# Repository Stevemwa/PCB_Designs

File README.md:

# ALTIMETER

# IP-SNIFFER

# LCD BEEPER

# PI ZERO SENSOR SHIELD

# I2C MOTOR DRIVER

# ESP32 DEV BOARD

# ATTINY85 ALARM

# AMPLIFIER WITH TUNNING

# TELEMETRIC DASHCAM PCB

# STM32 WIFI BOARD FOR SMART BMS

# NFC MODEL TRAIN

# ROBOKEN PCB

# CAMERA TRAP PROTOTYPE

# DIMM DDR3 TESTER

# VEHICLE TRACKERS

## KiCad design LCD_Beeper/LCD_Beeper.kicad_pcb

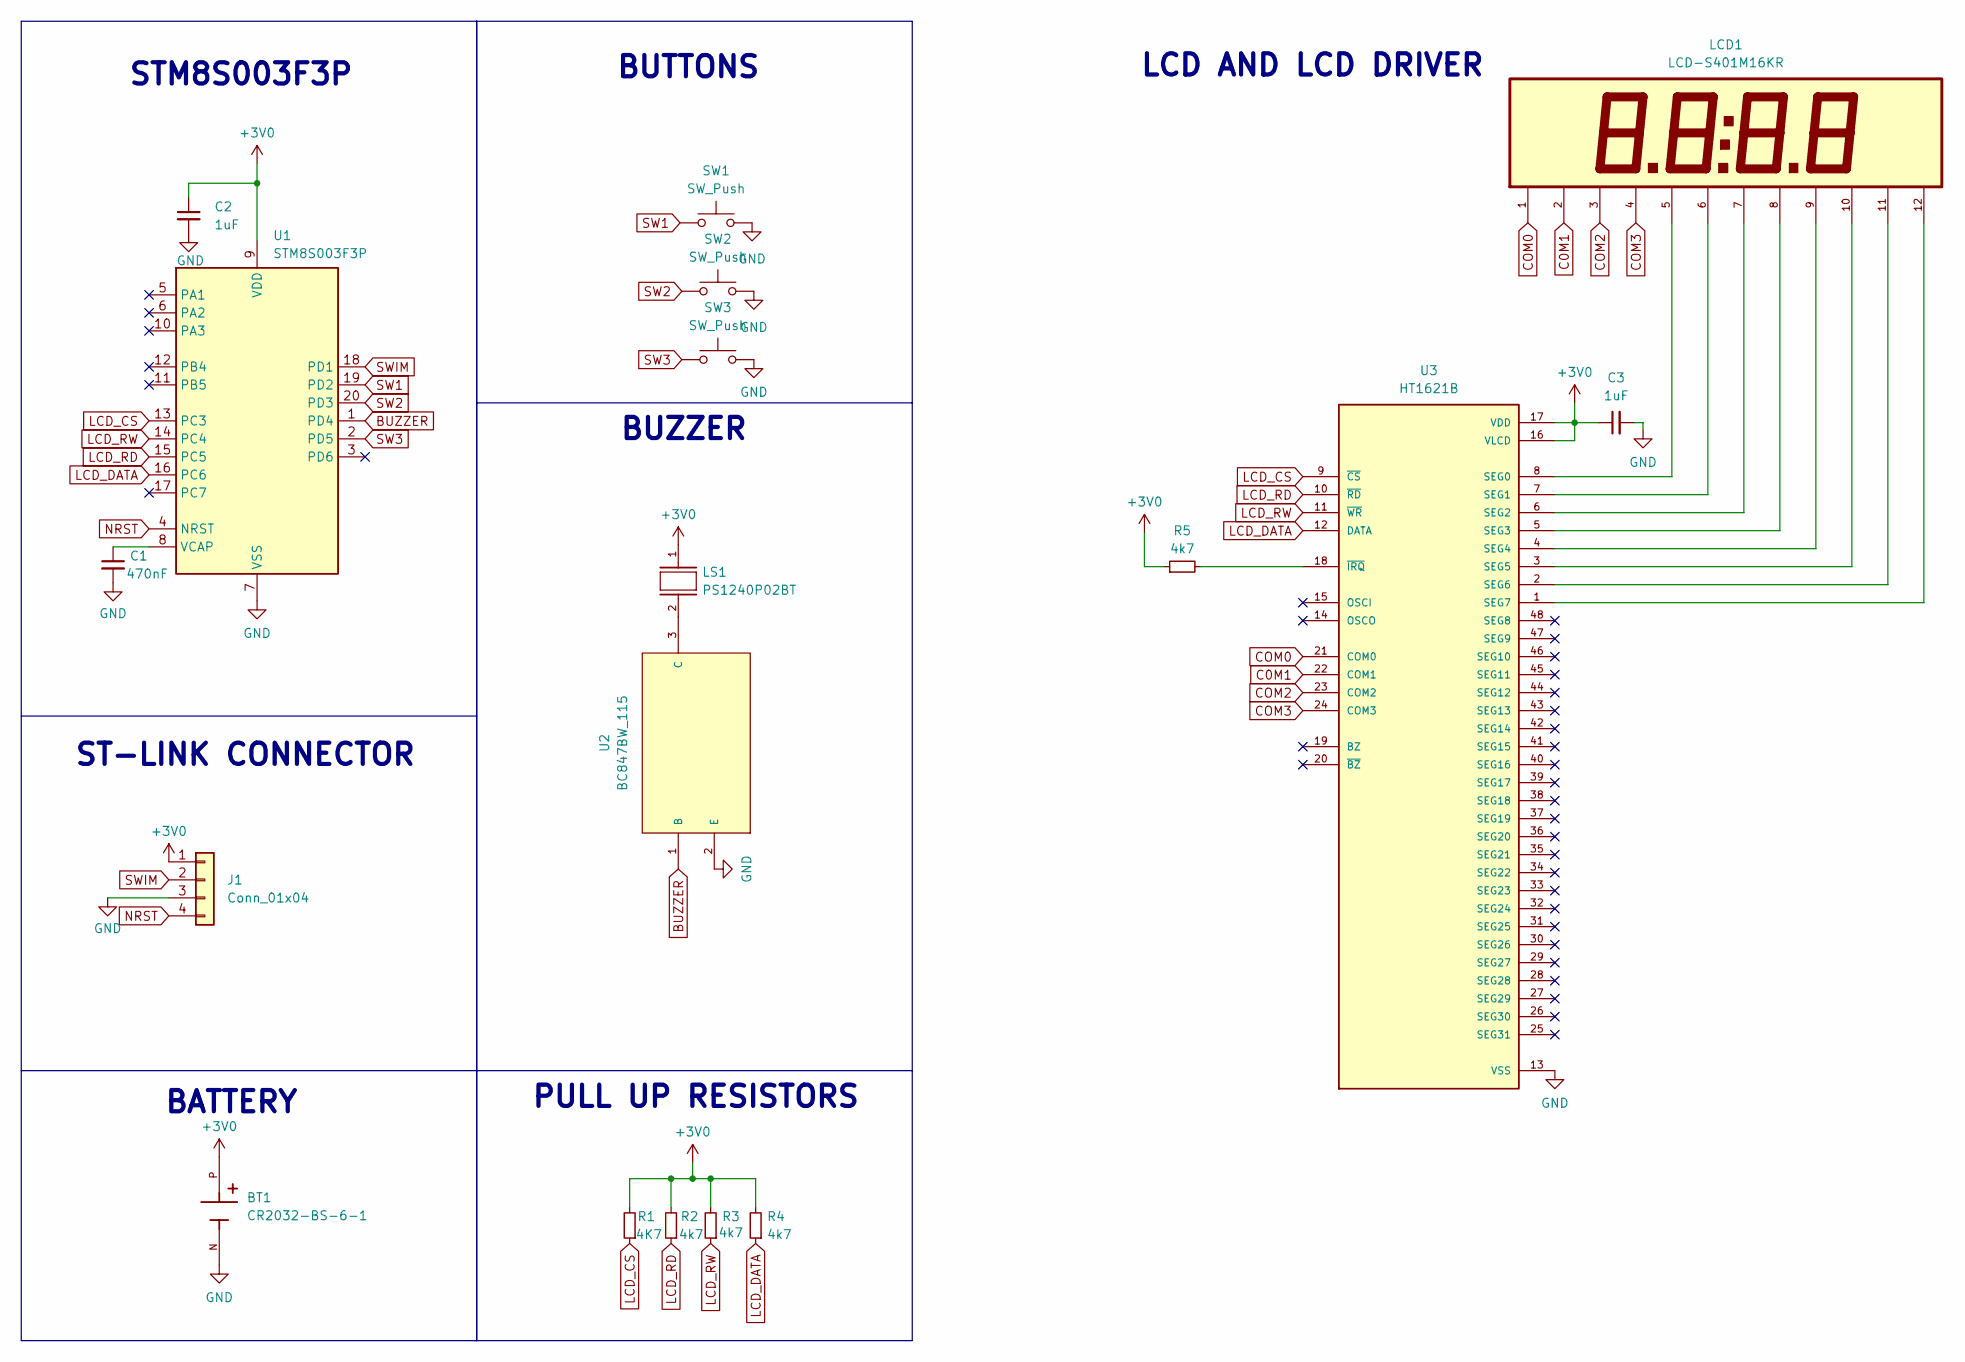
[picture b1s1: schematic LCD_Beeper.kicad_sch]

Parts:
BT1: CR2032-BS-6-1; BAT_CR2032-BS-6-1; PARTREV 2011/2/14
C1: 470nF; C_0603_1608Metric
C2, C3: 1uF; C_0805_2012Metric
J1: Conn_01x04; PinHeader_1x04_P2.54mm_Horizontal
LCD1: LCD-S401M16KR; LCD_Aliexpress
LS1: PS1240P02BT; Buzzer_PS1240P02BT
R1: 4K7; R_0603_1608Metric
R2, R3, R4, R5: 4k7; R_0603_1608Metric
SW1, SW2, SW3: SW_Push; Butn
U1: STM8S003F3P; TSSOP-20_4.4x6.5mm_P0.65mm
U2: BC847BW_115; SO65P210X100-3N; MPN BC847BW,115
U3: HT1621B; HT1621B_SOP63P1035X279-48N; PARTREV 3.21

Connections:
+3V0: BT1.P, C2.1, C3.1, J1.1, LS1.1, R1.2, R2.2, R3.2, R4.2, R5.1, U1.9 (VDD), U3.16 (VLCD), U3.17 (VDD)
BUZZER: U1.1 (PD4), U2.1 (B)
C0M1: LCD1.2, U3.22 (COM1)
COM0: LCD1.1, U3.21 (COM0)
COM2: LCD1.3, U3.23 (COM2)
COM3: LCD1.4, U3.24 (COM3)
GND: BT1.N, C1.2, C2.2, C3.2, J1.3, SW1.2, SW2.2, SW3.2, U1.7 (VSS), U2.2 (E), U3.13 (VSS)
LCD_CS: R1.1, U1.13 (PC3), U3.9 (~CS)
LCD_DATA: R4.1, U1.16 (PC6), U3.12 (DATA)
LCD_RD: R2.1, U1.15 (PC5), U3.10 (~RD)
LCD_RW: R3.1, U1.14 (PC4), U3.11 (~WR)
NRST: J1.4, U1.4 (NRST)
unnamed: C1.1, U1.8 (VCAP)
unnamed: LS1.2, U2.3 (C)
unnamed: LCD1.5, U3.8 (SEG0)
unnamed: LCD1.6, U3.7 (SEG1)
unnamed: LCD1.7, U3.6 (SEG2)
unnamed: LCD1.8, U3.5 (SEG3)
unnamed: LCD1.9, U3.4 (SEG4)
unnamed: LCD1.10, U3.3 (SEG5)
unnamed: LCD1.11, U3.2 (SEG6)
unnamed: LCD1.12, U3.1 (SEG7)
unnamed: R5.2, U3.18 (~IRQ)
SW1: SW1.1, U1.19 (PD2)
SW2: SW2.1, U1.20 (PD3)
SW3: SW3.1, U1.2 (PD5)
SWIM: J1.2, U1.18 (PD1)

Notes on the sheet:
PULL UP RESISTORS
LCD AND LCD DRIVER
BUTTONS
ST-LINK CONNECTOR
STM8S003F3P
BATTERY
BUZZER

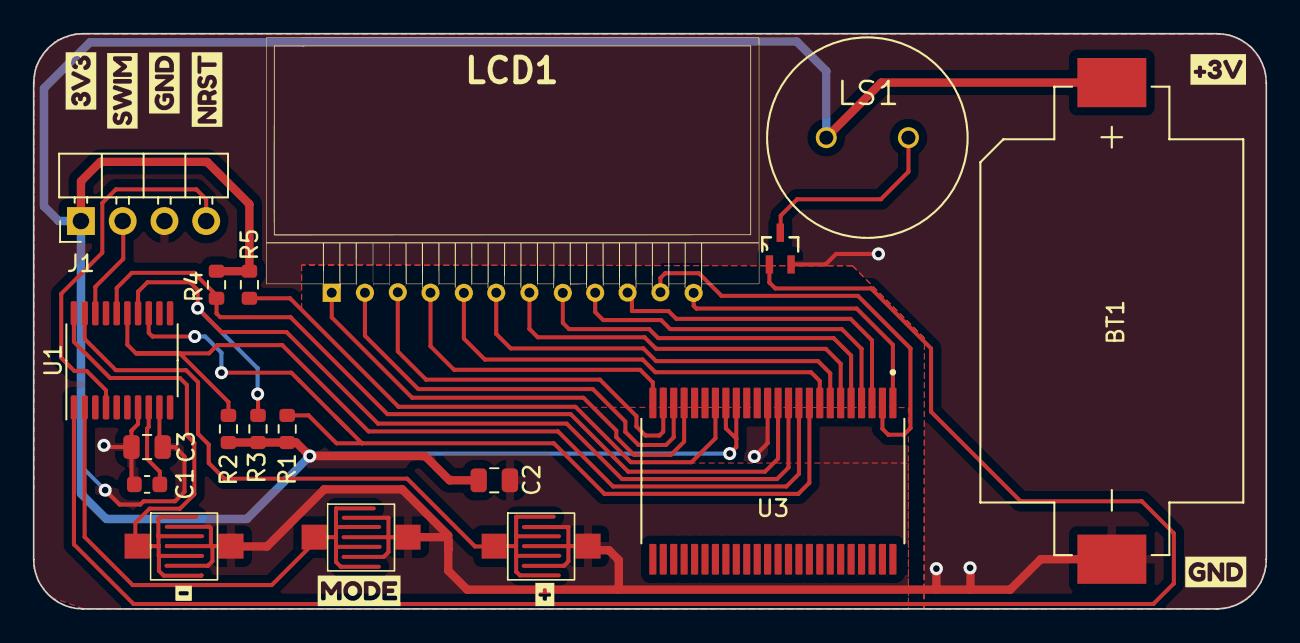
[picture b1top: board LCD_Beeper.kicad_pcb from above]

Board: 2 copper layers, 75.0 x 35.0 mm, 27 parts (0 on the bottom side), 27 nets.

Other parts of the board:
kibuzzard-669CD0A9: G***; kibuzzard-669CD0A9
kibuzzard-669CD0BB: G***; kibuzzard-669CD0BB
kibuzzard-669CD0D2: G***; kibuzzard-669CD0D2
kibuzzard-669CD0EA: G***; kibuzzard-669CD0EA
kibuzzard-669D55EF: G***; kibuzzard-669D55EF
kibuzzard-669D561E: G***; kibuzzard-669D561E
kibuzzard-669D5618: G***; kibuzzard-669D5618
kibuzzard-669E5857: G***; kibuzzard-669E5857
kibuzzard-669E5870: G***; kibuzzard-669E5870

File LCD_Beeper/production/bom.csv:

Designator,Footprint,Quantity,Value,JLCPCB Part #
BT1,SMD,1,CR2032-BS-6-1,C70377
C1,603,1,50V 470nF X7R ±10%,C77572
"C2, C3",805,2,1uF,C89259
J1,"Push-Pull,P=2.54mm",1,PinHeader_1x04_P2.54mm_Horizontal,C91552
LS1,"Plugin,D=12.2mm",1,PS1240P02BT,C76871
"R1, R2, R3, R4, R5",603,5,50V ±25ppm/? ±0.1% 4.7k? 0603 ,C666997
"SW1, SW2, SW3",Butn,3,SW_Push,
U1,TSSOP-20,1,STM8S003F3P,C18615
U2,SOT-323,1,BC847BW_115,C2836072
U3,SSOP-48-300mil,1,HT1621B,C7873

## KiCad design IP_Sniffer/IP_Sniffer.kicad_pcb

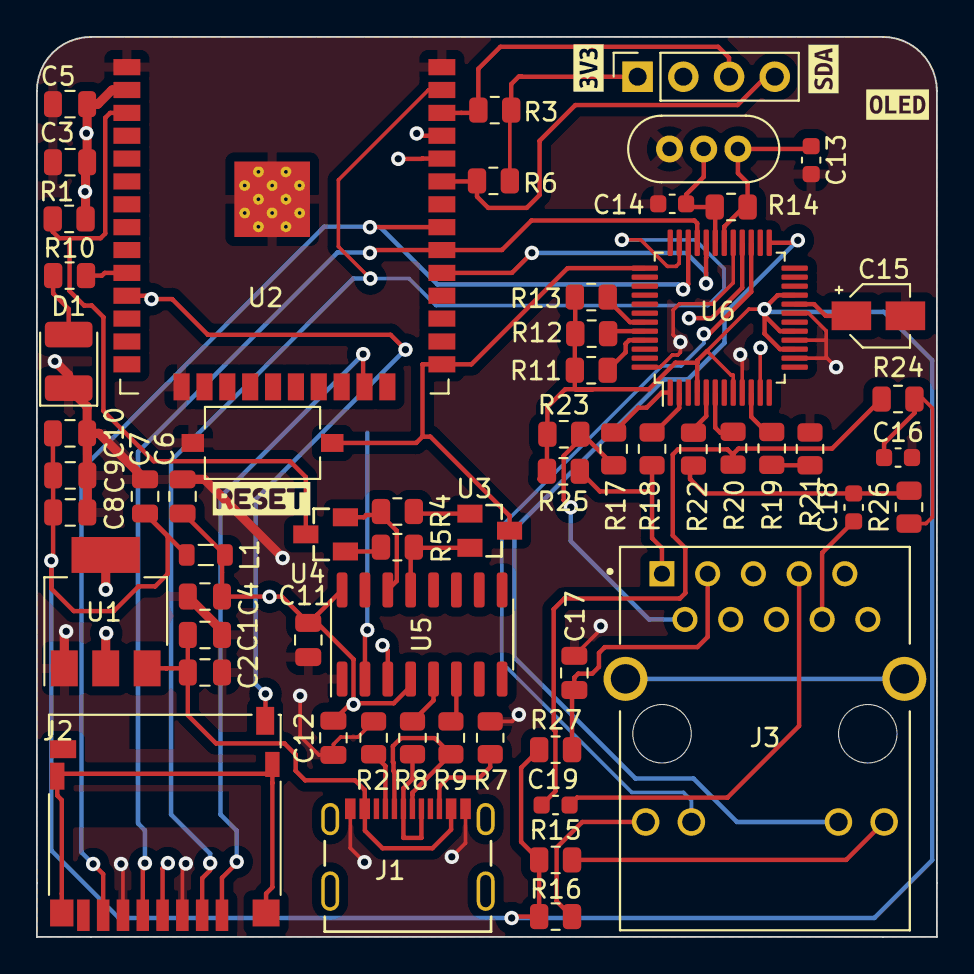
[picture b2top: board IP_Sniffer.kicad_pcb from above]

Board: 4 copper layers, 50.0 x 50.0 mm, 64 parts (0 on the bottom side), 52 nets.

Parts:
C1, C6: 100uF; C_0805_2012Metric
C2, C4, C7, C8, C9, C12: 100nF; C_0805_2012Metric
C3: 1uF; C_0805_2012Metric
C5, C10: 10uF; C_0805_2012Metric
C11: 100nf; C_0805_2012Metric
C13, C14: 12pF; C_0603_1608Metric
C15: 4u7; CP_Elec_3x5.3
C16: 10n; C_0603_1608Metric
C17: 100n; C_0805_2012Metric
C18, C19: 6.8n; C_0603_1608Metric
D1: LED_Small; LED_1210_3225Metric_Pad1.42x2.65mm_HandSolder
J1: 2171790001; USB_C_MOLEX
J2: SD_Card; microSD_HC_Hirose_DM3D-SF
J3: HR911130A; RJ45_HANRUN_HR911130A
J4: Conn_01x04; PinSocket_1x04_P2.54mm_Vertical
L1: 10uH; L_0805_2012Metric
R1, R2, R3, R6, R7, R10, R19, R21: 5k1; R_0805_2012Metric
R4, R5, R11, R12, R13: 10k; R_0805_2012Metric
R8, R9, R17, R18, R20, R22: 33; R_0805_2012Metric
R14: 1M; R_0805_2012Metric
R15, R16: 330R; R_0805_2012Metric
R23, R24, R25, R26: 49R9/1%; R_0805_2012Metric
R27: 10R/1%; R_0805_2012Metric
SW1: SW_Push; SW_Tactile_SPST_NO_Straight_CK_PTS636Sx25SMTRLFS
U1: AMS1117; SOT-223-3_TabPin2
U2: ESP32-WROOM-32
U3, U4: IRLML2502TRPBF; SOT23
U5: CH340C; SOIC-16_3.9x9.9mm_P1.27mm
U6: W5500; LQFP-48_7x7mm_P0.5mm
Y1: 25MHz; Crystal_HC52-U-3Pin_Vertical
kibuzzard-66784B35: G***; kibuzzard-66784B35
kibuzzard-667847D2: G***; kibuzzard-667847D2
kibuzzard-667847FB: G***; kibuzzard-667847FB
kibuzzard-667858E3: G***; kibuzzard-667858E3

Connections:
+3.3VA: C7.1, C8.1, C9.1, C10.1, L1.2, R11.1, R12.1, R13.1, R15.1, R16.1, R23.2, R25.2, R27.2, U6.4 (AVDD), U6.8 (AVDD), U6.11 (AVDD), U6.15 (AVDD), U6.17 (AVDD), U6.21 (AVDD)
+3V3: C3.1, C4.1, C5.1, C6.1, C11.2, C12.1, J2.4 (VDD), J4.1, L1.1, R1.1, R3.1, R6.1, U1.2 (VO), U2.2 (VDD), U5.4 (V3), U5.16 (VCC), U6.28 (VDD)
+5V: C1.1, C2.1, J1.A4B9 (VBUS1), J1.B4A9 (VBUS2), U1.3 (VI)
CARD_DETECT: J2.10 (CARD_DETECT), U2.11 (IO26)
DTR: R5.1, U3.2, U5.13 (~DTR)
EN: R1.2, U2.3 (EN), U4.3
ESP-RX: U2.34 (RXD0/IO3), U5.2 (TXD)
ESP-TX: U2.35 (TXD0/IO1), U5.3 (RXD)
GND: C1.2, C2.2, C3.2, C4.2, C5.2, C6.2, C7.2, C8.2, C9.2, C10.2, C11.1, C12.2, C13.2, C14.1, C15.2, C16.2, C17.2, D1.1 (K), J1.A1B12 (GND1), J1.B1A12 (GND2), J2.3 (VSS), J2.6 (VSS), J4.2, R2.1, R7.2, R21.2, SW1.2, U1.1 (ADJ), U2.1 (GND), U2.15 (GND), U2.38 (GND), U2.39 (GND), U5.1 (GND), U6.3 (AGND), U6.9 (AGND), U6.14 (AGND), U6.16 (AGND), U6.19 (AGND), U6.29 (GND), U6.48 (AGND), Y1.3
IO0: SW1.1, U2.25 (IO0), U3.3, U6.37 (~RST)
IO25: R10.1, U2.10 (IO25)
MISO: J2.7 (DAT0), U2.31 (IO19), U6.34 (MISO)
MOSI: J2.2 (CMD), U2.37 (IO23), U6.35 (MOSI)
unnamed: C16.1, R24.1, R26.1
unnamed: C18.1, R22.1, R26.2
unnamed: C19.1, R20.2, R24.2
unnamed: D1.2 (A), R10.2
unnamed: J1.A5 (CC1), R2.2
unnamed: J1.B5 (CC2), R7.1
unnamed: J3.11, R16.2
unnamed: J3.14, R15.2
unnamed: R4.2, U3.1
unnamed: R5.2, U4.1
unnamed: R19.2, R21.1
unnamed: R8.2, U5.5 (UD+)
unnamed: R9.2, U5.6 (UD-)
unnamed: R19.1, U6.10 (EXRES1)
unnamed: R11.2, U6.45 (PMODE0)
unnamed: R12.2, U6.44 (PMODE1)
unnamed: R13.2, U6.43 (PMODE2)
unnamed: R22.2, U6.5 (RXN)
unnamed: R20.1, U6.6 (RXP)
unnamed: C15.1, U6.20 (TOCAP)
unnamed: R17.2, U6.1 (TXN)
unnamed: R18.1, U6.2 (TXP)
unnamed: C13.1, R14.2, U6.30 (XI/CLKIN), Y1.1
unnamed: C14.2, R14.1, U6.31 (XO), Y1.2
R1: J3.1, R18.2, R25.1
R2: J3.2, R17.1, R23.1
R3: C17.1, J3.3, R27.1
R7: C19.2, J3.7
R8: C18.2, J3.8
RTS: R4.1, U4.2, U5.14 (~RTS)
SCK: J2.5 (CLK), U2.30 (IO18), U6.33 (SCLK)
SCL: J4.3, R3.2, U2.36 (IO22)
SDA: J4.4, R6.2, U2.33 (IO21)
SS1: U2.29 (IO5), U6.32 (~SCS)
SS2: J2.1 (CD/DAT3), U2.23 (IO15)
USB_D+: J1.A6 (DP1), J1.B6 (DP2), R8.1
USB_D-: J1.A7 (DN1), J1.B7 (DN2), R9.1
actled: J3.12, U6.27 (ACTLED)
linkled: J3.13, U6.25 (LINKLED)

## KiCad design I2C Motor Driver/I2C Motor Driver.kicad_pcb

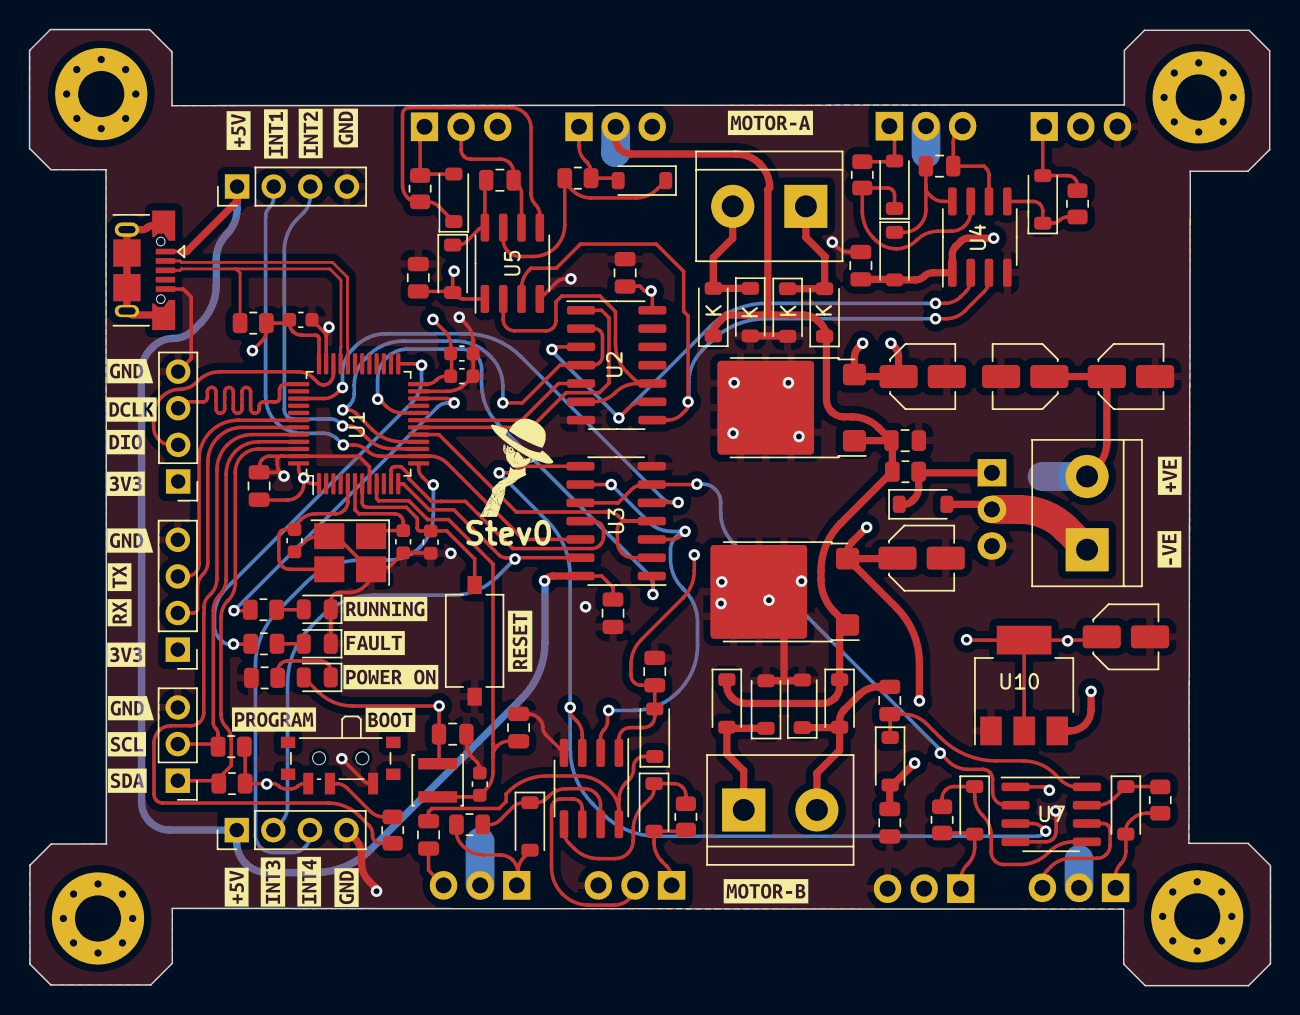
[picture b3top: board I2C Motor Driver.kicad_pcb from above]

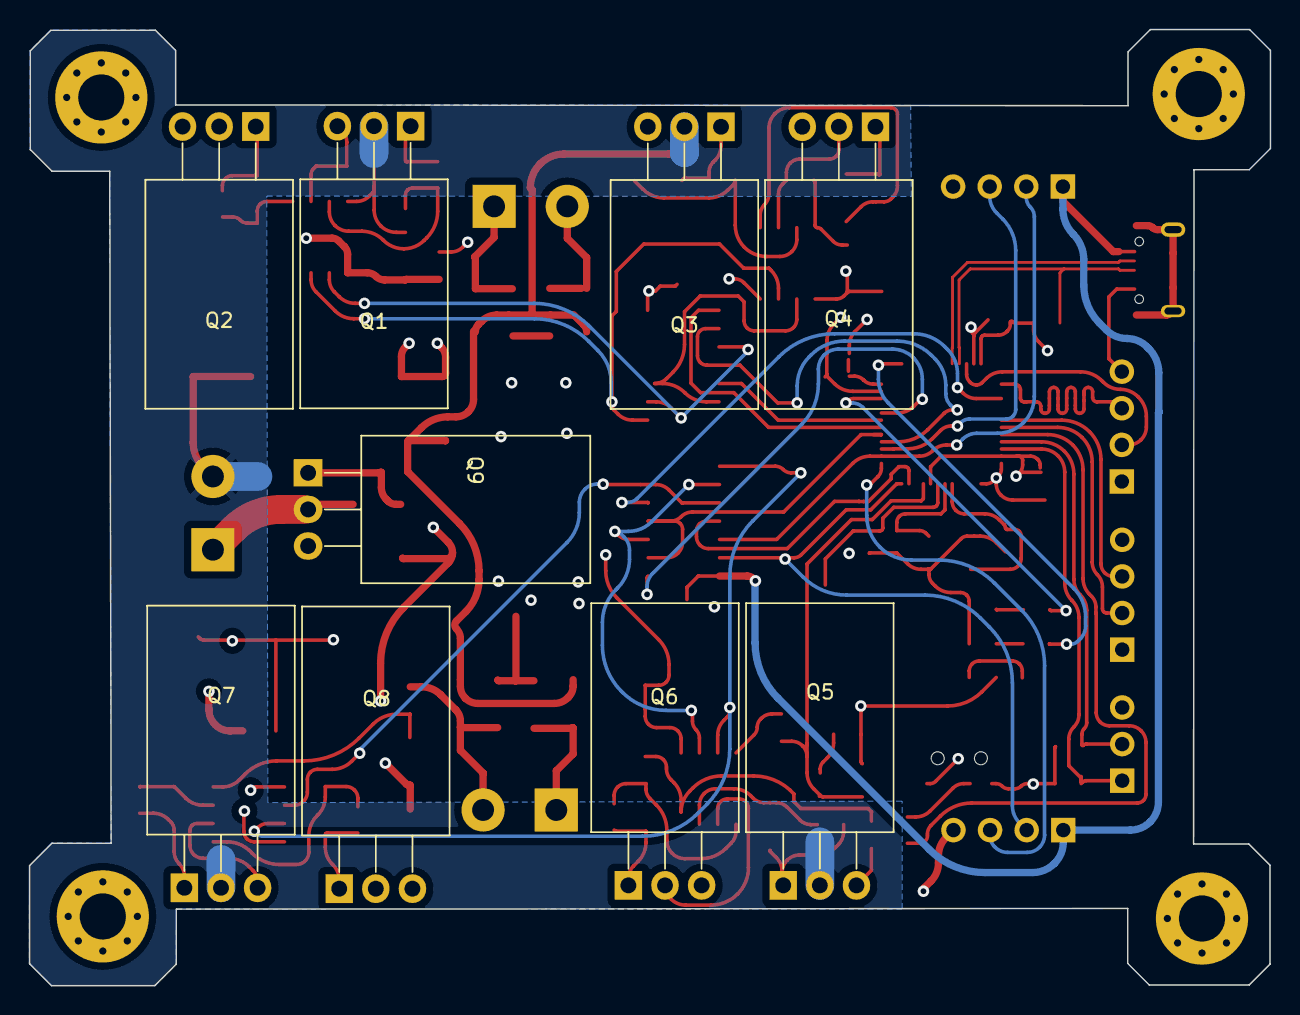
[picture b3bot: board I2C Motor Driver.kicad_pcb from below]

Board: 4 copper layers, 86.1 x 66.3 mm, 132 parts (9 on the bottom side), 67 nets.

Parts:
C1, C22: 10uF; C_0805_2012Metric
C2, C3, C4, C8: 100nF; C_0603_1608Metric
C5, C7, C11, C14, C15, C18, C25, C26: 1uF; C_0805_2012Metric
C6: 10nF; C_0603_1608Metric
C9, C10: 10pF; C_0603_1608Metric
C12, C13, C16, C17: 1.5uF; C_0805_2012Metric
C19: 100uF; C_Elec_4x5.4
C20, C21, C23, C24: 22uF; C_Elec_4x5.4
D1: BLUE; LED_0805_2012Metric
D2: GREEN; LED_0805_2012Metric
D3, D12, D13, D22: D; D_SOD-123
D4, D5, D10, D11, D14, D15, D20, D21: 1N4148; D_SOD-123
D6, D7, D8, D9, D16, D17, D18, D19: 1N5819; D_SOD-123
D23: 15v; D_SOD-123
D24: RED; LED_0805_2012Metric
FB1: 120R; L_Changjiang_FNR3010S
H1, H2, H3, H4: MountingHole_Pad; MountingHole_3.2mm_M3_Pad_Via
J1, J3: SWD; PinHeader_1x04_P2.54mm_Vertical
J2, J6: Conn_01x04_Pin; PinHeader_1x04_P2.54mm_Vertical
J4: Conn_01x03_Pin; PinHeader_1x03_P2.54mm_Vertical
J5: USB_B_Micro; USB_Micro-B_XKB_U254-051T-4BH83-F1S
J7: MOTOR_A; TerminalBlock_bornier-2_P5.08mm
J8: MOTOR_B; TerminalBlock_bornier-2_P5.08mm
J9: +24V_INPUT; TerminalBlock_bornier-2_P5.08mm
Q1, Q2, Q3, Q4, Q5, Q6, Q7, Q8, Q9: IRLZ44N; TO-220-3_Horizontal_TabDown
R1, R15: 10k; R_0805_2012Metric
R2, R3, R4, R5, R6, R16: 1K5; R_0805_2012Metric
R7, R8, R9, R10, R11, R12, R13, R14: 30R; R_0805_2012Metric
SW1: SW_DPST_x2; SW_Tactile_SPST_NO_Straight_CK_PTS636Sx25SMTRLFS
SW2: SW_SPDT; SW_SPDT_PCM12
Stev0: LOGO; Luffy6by6
U1: STM32F103C8Tx; LQFP-48_7x7mm_P0.5mm
U2, U3: 7400; SOIC-14_3.9x8.7mm_P1.27mm
U4, U5, U6, U7: IR2104; SOIC-8_3.9x4.9mm_P1.27mm
U8: L7805; ATPAK-2
U9: L7815; ATPAK-2
U10: AMS1117-3.3; SOT-223-3_TabPin2
Y1: 16MHz; Crystal_SMD_3225-4Pin_3.2x2.5mm_HandSoldering
kibuzzard-664F1B6E: G***; kibuzzard-664F1B6E
kibuzzard-664F1B57: G***; kibuzzard-664F1B57
kibuzzard-664F4C94: G***; kibuzzard-664F4C94
kibuzzard-664F4D60: G***; kibuzzard-664F4D60
kibuzzard-664F4D77: G***; kibuzzard-664F4D77
kibuzzard-664F4DB5: G***; kibuzzard-664F4DB5
kibuzzard-664F4E3A: G***; kibuzzard-664F4E3A
kibuzzard-664F4F6B: G***; kibuzzard-664F4F6B
kibuzzard-664F4F90: G***; kibuzzard-664F4F90
kibuzzard-664F19CD: G***; kibuzzard-664F19CD
kibuzzard-664F19D9: G***; kibuzzard-664F19D9
kibuzzard-664F19F6, kibuzzard-664F19F6#2: G***; kibuzzard-664F19F6
kibuzzard-664F35B9: G***; kibuzzard-664F35B9
kibuzzard-664F47C9: G***; kibuzzard-664F47C9
kibuzzard-664F49B2: G***; kibuzzard-664F49B2
kibuzzard-664F49D0: G***; kibuzzard-664F49D0
kibuzzard-664F52A3: G***; kibuzzard-664F52A3
kibuzzard-664F52AD: G***; kibuzzard-664F52AD
kibuzzard-664F88B5: G***; kibuzzard-664F88B5
kibuzzard-664F88D1: G***; kibuzzard-664F88D1
kibuzzard-664F88FA: G***; kibuzzard-664F88FA
kibuzzard-664F354C: G***; kibuzzard-664F354C
kibuzzard-664F878C: G***; kibuzzard-664F878C
kibuzzard-664F3565: G***; kibuzzard-664F3565
kibuzzard-664F8782: G***; kibuzzard-664F8782
kibuzzard-664F8796: G***; kibuzzard-664F8796
kibuzzard-664F8901: G***; kibuzzard-664F8901
kibuzzard-664FF9FF: G***; kibuzzard-664FF9FF

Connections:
+3.3V: C1.1, C2.1, C3.1, C4.1, C7.1, C24.1, D24.2 (A), FB1.1, J1.1, J3.1, R2.2, R5.2, R6.2, SW2.3 (C), U1.1 (VBAT), U1.24 (VDD), U1.36 (VDD), U1.48 (VDD), U10.2 (VO)
+5V: C21.1, C25.1, C26.1, J2.1, J5.1 (VBUS), J6.1, U2.14 (VCC), U3.14 (VCC), U8.3 (OUT)
+15V: C11.1, C14.1, C15.1, C18.1, C23.1, D3.2 (A), D12.2 (A), D13.2 (A), D22.2 (A), U4.1 (VCC), U5.1 (VCC), U6.1 (VCC), U7.1 (VCC), U9.3 (OUT), U10.3 (VI)
+24V: C19.1, C20.1, C22.1, D6.1 (K), D8.1 (K), D16.1 (K), D18.1 (K), J9.2, Q1.2 (D), Q3.2 (D), Q5.2 (D), Q7.2 (D), R15.1, U8.1 (IN), U9.1 (IN)
/Dual_HBridge/HC1: C16.2, D16.2 (A), D17.1 (K), J8.1, Q5.3 (S), Q6.2 (D), U6.6 (VS)
/Dual_HBridge/HC2: C17.2, D18.2 (A), D19.1 (K), J8.2, Q7.3 (S), Q8.2 (D), U7.6 (VS)
/Dual_HBridge/HC3: C12.2, D6.2 (A), D7.1 (K), J7.1, Q1.3 (S), Q2.2 (D), U4.6 (VS)
/Dual_HBridge/HC4: C13.2, D8.2 (A), D9.1 (K), J7.2, Q3.3 (S), Q4.2 (D), U5.6 (VS)
BLUE_LED: R3.1, U1.25 (PB12)
BOOT0: R1.2, U1.44 (BOOT0)
ENA: U1.16 (PA6), U2.2, U2.4
ENB: U1.17 (PA7), U3.2, U3.4
EXT_INT0: U1.11 (PA1), U3.11
EXT_INT1: J2.2, U1.14 (PA4), U3.12
EXT_INT2: J2.3, U1.15 (PA5)
EXT_INT3: J6.2, U1.12 (PA2), U3.13
EXT_INT4: J6.3, U1.13 (PA3)
GND: C1.2, C2.2, C3.2, C4.2, C5.2, C6.2, C7.2, C8.2, C9.2, C10.2, C11.2, C14.2, C15.2, C18.2, C19.2, C20.2, C21.2, C22.2, C23.2, C24.2, C25.2, C26.2, D1.1 (K), D2.1 (K), D7.2 (A), D9.2 (A), D17.2 (A), D19.2 (A), J1.4, J2.4, J3.4, J4.3, J5.5 (GND), J6.4, Q2.3 (S), Q4.3 (S), Q6.3 (S), Q8.3 (S), Q9.3 (S), R16.2, SW1.1 (A), SW2.1 (A), U1.8 (VSSA), U1.23 (VSS), U1.35 (VSS), U1.47 (VSS), U2.7 (GND), U3.7 (GND), U4.4 (COM), U5.4 (COM), U6.4 (COM), U7.4 (COM), U8.2 (GND), U9.2 (GND), U10.1 (GND), Y1.2, Y1.4
GREEN_LED: R4.1, U1.22 (PB11)
HSE_IN: C10.1, U1.5 (PD0), Y1.3
HSE_OUT: C9.1, U1.6 (PD1), Y1.1
I2C_SCL: J4.2, R5.1, U1.45 (PB8)
I2C_SDA: J4.1, R6.1, U1.46 (PB9)
IN1: U1.18 (PB0), U2.1
IN2: U1.19 (PB1), U2.5
IN3: U1.20 (PB2), U3.1
IN4: U1.39 (PB3), U3.5
NRST: C8.1, SW1.2 (B), U1.7 (NRST)
unnamed: D1.2 (A), R3.2
unnamed: D2.2 (A), R4.2
unnamed: C12.1, D3.1 (K), U4.8 (VB)
unnamed: D4.2 (A), Q2.1 (G), R7.2
unnamed: D4.1 (K), R7.1, U4.5 (LO)
unnamed: D5.2 (A), Q1.1 (G), R8.2
unnamed: D5.1 (K), R8.1, U4.7 (HO)
unnamed: D10.2 (A), Q3.1 (G), R9.2
unnamed: D10.1 (K), R9.1, U5.7 (HO)
unnamed: D11.2 (A), Q4.1 (G), R10.2
unnamed: D11.1 (K), R10.1, U5.5 (LO)
unnamed: C13.1, D12.1 (K), U5.8 (VB)
unnamed: C16.1, D13.1 (K), U6.8 (VB)
unnamed: D14.2 (A), Q6.1 (G), R11.2
unnamed: D14.1 (K), R11.1, U6.5 (LO)
unnamed: D15.2 (A), Q5.1 (G), R12.2
unnamed: D15.1 (K), R12.1, U6.7 (HO)
unnamed: D20.2 (A), Q7.1 (G), R13.2
unnamed: D20.1 (K), R13.1, U7.7 (HO)
unnamed: D21.2 (A), Q8.1 (G), R14.2
unnamed: D21.1 (K), R14.1, U7.5 (LO)
unnamed: C17.1, D22.1 (K), U7.8 (VB)
unnamed: D23.2 (A), J9.1, Q9.2 (D)
unnamed: D23.1 (K), Q9.1 (G), R15.2
unnamed: D24.1 (K), R16.1
unnamed: R1.1, SW2.2 (B)
unnamed: C5.1, C6.1, FB1.2, U1.9 (VDDA)
unnamed: U2.3, U2.9, U4.2 (IN)
unnamed: U2.8, U4.3 (~SD), U5.3 (~SD)
unnamed: U2.6, U2.10, U5.2 (IN)
unnamed: U3.3, U3.9, U6.2 (IN)
unnamed: U3.8, U6.3 (~SD), U7.3 (~SD)
unnamed: U3.6, U3.10, U7.2 (IN)
SWCLK: J1.3, U1.37 (PA14)
SWDIO: J1.2, U1.34 (PA13)
UART1_RX: J3.2, U1.43 (PB7)
UART1_TX: J3.3, U1.42 (PB6)
USB_D+: J5.3 (D+), R2.1, U1.33 (PA12)
USB_D-: J5.2 (D-), U1.32 (PA11)

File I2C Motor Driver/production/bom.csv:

Designator,Footprint,Quantity,Value,LCSC Part #
"C1, C22",0805,2,10uF,
"C10, C9",0603,2,10pF,
"C11, C14, C15, C18, C5, C7",0805,6,1uF,
"C12, C13, C16, C17",0805,4,1.5uF,
C19,C_Elec_4x5.4,1,100uF,
"C2, C3, C4, C8",0603,4,100nF,
"C20, C21, C23, C24",C_Elec_4x5.4,4,22uF,
C6,0603,1,10nF,
D1,0805,1,BLUE,
"D10, D11, D14, D15, D20, D21, D4, D5",D_SOD-123,8,1N4148,
"D12, D13, D22, D3",D_SOD-123,4,D,
"D16, D17, D18, D19, D6, D7, D8, D9",D_SOD-123,8,1N5819,
D2,0805,1,GREEN,
D23,D_SOD-123,1,15v,
D24,0805,1,RED,
FB1,L_Changjiang_FNR3010S,1,120R,
"H1, H2, H3, H4",MountingHole_3.2mm_M3_Pad_Via,4,MountingHole_Pad,
"J1, J3",PinHeader_1x04_P2.54mm_Vertical,2,SWD,
"J2, J6",PinHeader_1x04_P2.54mm_Vertical,2,Conn_01x04_Pin,
J4,PinHeader_1x03_P2.54mm_Vertical,1,Conn_01x03_Pin,
J5,USB_Micro-B_XKB_U254-051T-4BH83-F1S,1,USB_B_Micro,
J7,TerminalBlock_bornier-2_P5.08mm,1,MOTOR_A,
J8,TerminalBlock_bornier-2_P5.08mm,1,MOTOR_B,
J9,TerminalBlock_bornier-2_P5.08mm,1,+24V_INPUT,
"Q1, Q2, Q3, Q4, Q5, Q6, Q7, Q8, Q9",TO-220-3_Horizontal_TabDown,9,IRLZ44N,
"R1, R15",0805,2,10k,
"R10, R11, R12, R13, R14, R7, R8, R9",0805,8,30R,
"R16, R2, R3, R4, R5, R6",0805,6,1K5,
SW1,SW_Tactile_SPST_NO_Straight_CK_PTS636Sx25SMTRLFS,1,SW_DPST_x2,
SW2,SW_SPDT_PCM12,1,SW_SPDT,
U1,LQFP-48_7x7mm_P0.5mm,1,STM32F103C8Tx,
U10,SOT-223-3_TabPin2,1,AMS1117-3.3,
"U2, U3",SOIC-14_3.9x8.7mm_P1.27mm,2,7400,
"U4, U5, U6, U7",SOIC-8_3.9x4.9mm_P1.27mm,4,IR2104,
U8,ATPAK-2,1,L7805,
U9,ATPAK-2,1,L7815,
Y1,Crystal_SMD_3225-4Pin_3.2x2.5mm_HandSoldering,1,16MHz,

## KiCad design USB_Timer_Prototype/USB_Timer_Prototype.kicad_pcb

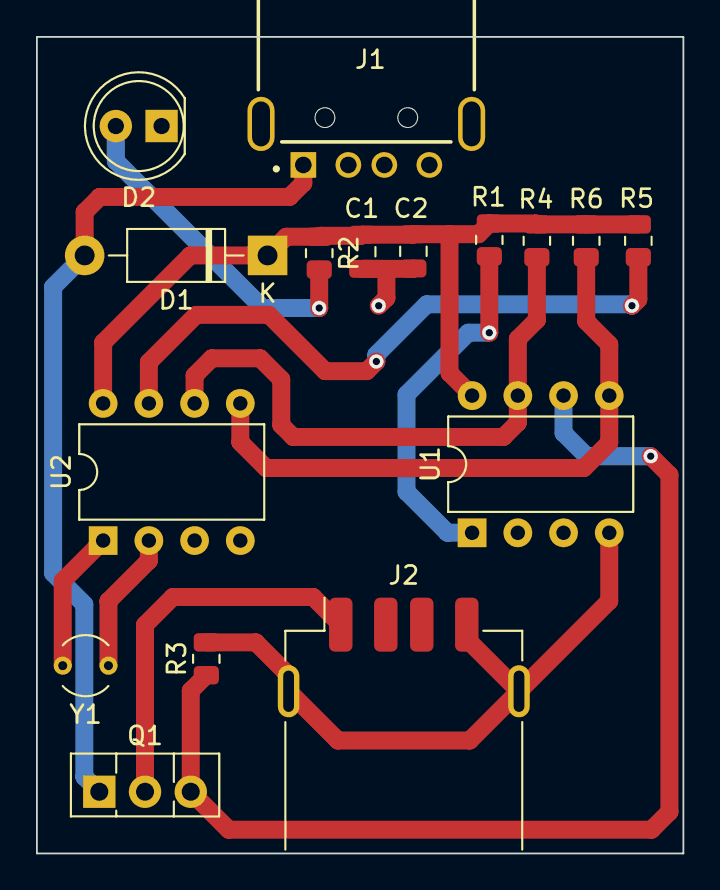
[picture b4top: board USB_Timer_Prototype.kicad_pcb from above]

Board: 2 copper layers, 35.9 x 45.4 mm, 16 parts (0 on the bottom side), 12 nets.

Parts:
C1: 0.1uF; C_0805_2012Metric
C2: 4.7uF; C_0805_2012Metric
D1: 1N4004; D_DO-41_SOD81_P10.16mm_Horizontal
D2: LED; LED_D5.0mm
J1: USB-AM-S-X-X-TH; SAMTEC_USB-AM-S-X-X-TH
J2: USB_A; USB_A_Receptacle_GCT_USB1046
Q1: BD136; TO-126-3_Vertical
R1, R2, R3: 10k; R_0805_2012Metric
R4, R5, R6: 4k7; R_0805_2012Metric
U1: ATtiny85-20P; DIP-8_W7.62mm
U2: DS1307+; DIP-8_W7.62mm
Y1: Crystal; Crystal_AT310_D3.0mm_L10.0mm_Vertical

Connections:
+5V: C1.1, C2.1, D1.1 (K), R1.2, R2.1, R4.1, R5.1, R6.1, U1.8 (VCC), U2.8 (VCC)
GND: C1.2, C2.2, D2.1 (K), J1.04 (GND), J1.S1 (SHIELD), J1.S2 (SHIELD), J2.4 (GND), J2.5 (Shield), R3.2, U1.4 (GND), U2.4 (GND)
unnamed: D1.2 (A), J1.01 (VCC), Q1.1 (E)
unnamed: D2.2 (A), R2.2
unnamed: J2.1 (VBUS), Q1.2 (C)
unnamed: R1.1, U1.1 (~RESET/PB5)
unnamed: R5.2, U2.7 (SQW/OUT)
unnamed: U2.1 (X1), Y1.2
unnamed: U2.2 (X2), Y1.1
SCL: R4.2, U1.7 (PB2), U2.6 (SCL)
SDA: R6.2, U1.5 (AREF/PB0), U2.5 (SDA)
mosfet: Q1.3 (B), R3.1, U1.6 (PB1)

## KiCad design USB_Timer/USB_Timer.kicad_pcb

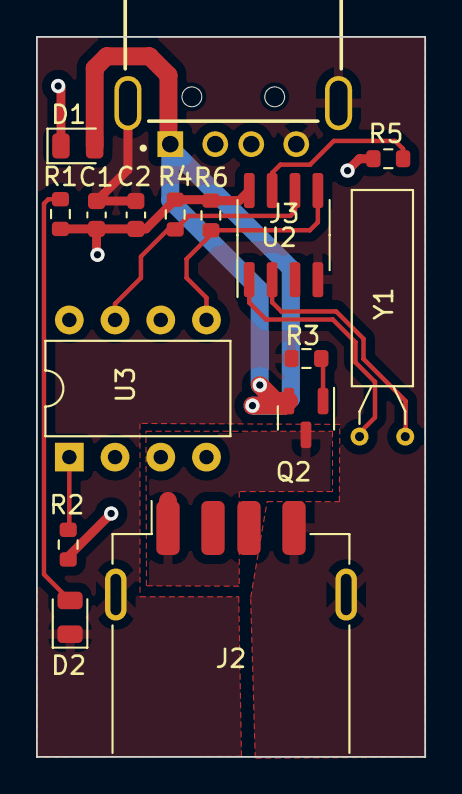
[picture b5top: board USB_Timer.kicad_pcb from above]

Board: 4 copper layers, 21.6 x 40.0 mm, 16 parts (0 on the bottom side), 12 nets.

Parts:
C1: 0.1uF; C_0603_1608Metric
C2: 4.7uF; C_0603_1608Metric
D1: 1N5819; D_0805_2012Metric
D2: LED; LED_0805_2012Metric
J2: USB_A; USB_A_Receptacle_GCT_USB1046
J3: USB-AM-S-X-X-TH; SAMTEC_USB-AM-S-X-X-TH
Q2: IRLML6401; SOT-23
R1, R2, R3: 10k; R_0603_1608Metric
R4, R5, R6: 4k7; R_0603_1608Metric
U2: DS1307Z+; SOIC-8_3.9x4.9mm_P1.27mm
U3: ATTINY85-20SU; DIP-8_W7.62mm
Y1: Crystal; Crystal_AT310_D3.0mm_L10.0mm_Horizontal

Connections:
+5V: C1.1, C2.1, D1.1 (K), R1.1, R2.2, R4.1, R5.1, R6.1, U2.8 (VCC), U3.8 (VCC)
GND: C1.2, C2.2, D2.1 (K), J2.4 (GND), J2.5 (Shield), J3.04 (GND), J3.S1 (SHIELD), J3.S2 (SHIELD), R3.2, U2.4 (GND), U3.4 (GND)
unnamed: D1.2 (A), J3.01 (VCC), Q2.2 (S)
unnamed: D2.2 (A), R1.2
unnamed: J2.1 (VBUS), Q2.3 (D)
unnamed: R5.2, U2.7 (SQW/OUT)
unnamed: U2.1 (X1), Y1.2
unnamed: U2.2 (X2), Y1.1
unnamed: R2.1, U3.1 (PB5)
SCL: R4.2, U2.6 (SCL), U3.7 (PB2)
SDA: R6.2, U2.5 (SDA), U3.5 (PB0)
mosfet: Q2.1 (G), R3.1

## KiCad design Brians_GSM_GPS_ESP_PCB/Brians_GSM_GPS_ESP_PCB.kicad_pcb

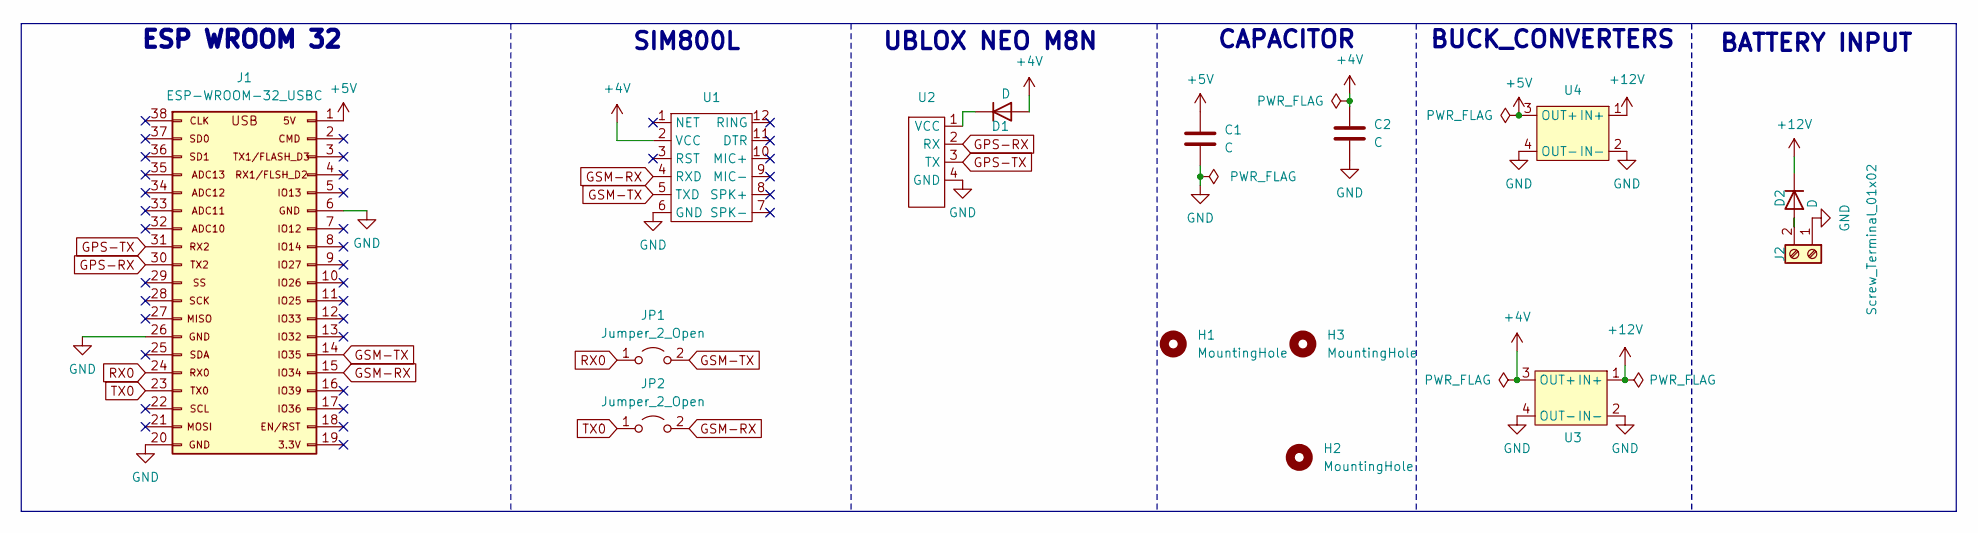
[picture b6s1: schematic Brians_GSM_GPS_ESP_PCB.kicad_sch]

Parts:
C1, C2: C; C_1206_3216Metric
D1, D2: D; D_5W_P10.16mm_Horizontal
H1, H2, H3: MountingHole; MountingHole_3.2mm_M3
J1: ESP-WROOM-32_USBC; ESP-WROOM-32 TYPE C
J2: Screw_Terminal_01x02; TerminalBlock_Altech_AK300-2_P5.00mm
JP1, JP2: Jumper_2_Open; TestPoint_2Pads_Pitch2.54mm_Drill0.8mm
U1: SIM800L_BOARD
U2: NEO_M8N_BOARD
U3, U4: BUCK CONVERTER

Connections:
+4V: C2.1, D1.2 (A), U1.2 (VCC), U3.3 (OUT+)
+5V: C1.1, J1.1 (5V), U4.3 (OUT+)
+12V: D2.1 (K), U3.1 (IN+), U4.1 (IN+)
GND: C1.2, C2.2, J1.6 (GND), J1.20 (GND), J1.26 (GND), J2.1, U1.6 (GND), U2.4 (GND), U3.2 (IN-), U3.4 (OUT-), U4.2 (IN-), U4.4 (OUT-)
GPS-RX: J1.30 (P17/TX2), U2.2 (RX)
GPS-TX: J1.31 (P16/RX2), U2.3 (TX)
GSM-RX: J1.15 (P34), JP2.2 (B), U1.4 (RXD)
GSM-TX: J1.14 (P35), JP1.2 (B), U1.5 (TXD)
unnamed: D1.1 (K), U2.1 (VCC)
unnamed: D2.2 (A), J2.2
RX0: J1.24 (P3/RX0), JP1.1 (A)
TX0: J1.23 (P1/TX0), JP2.1 (A)

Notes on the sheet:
UBLOX NEO M8N
CAPACITOR
BUCK_CONVERTERS
BATTERY INPUT
ESP WROOM 32
SIM800L

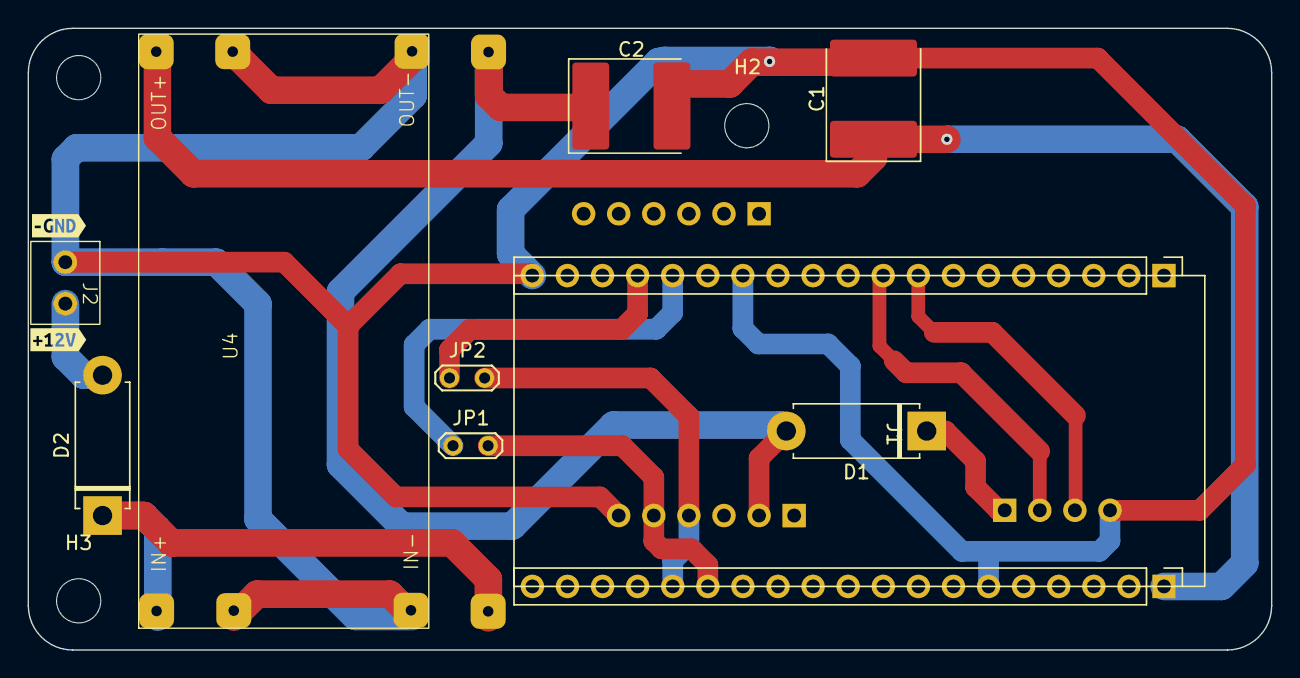
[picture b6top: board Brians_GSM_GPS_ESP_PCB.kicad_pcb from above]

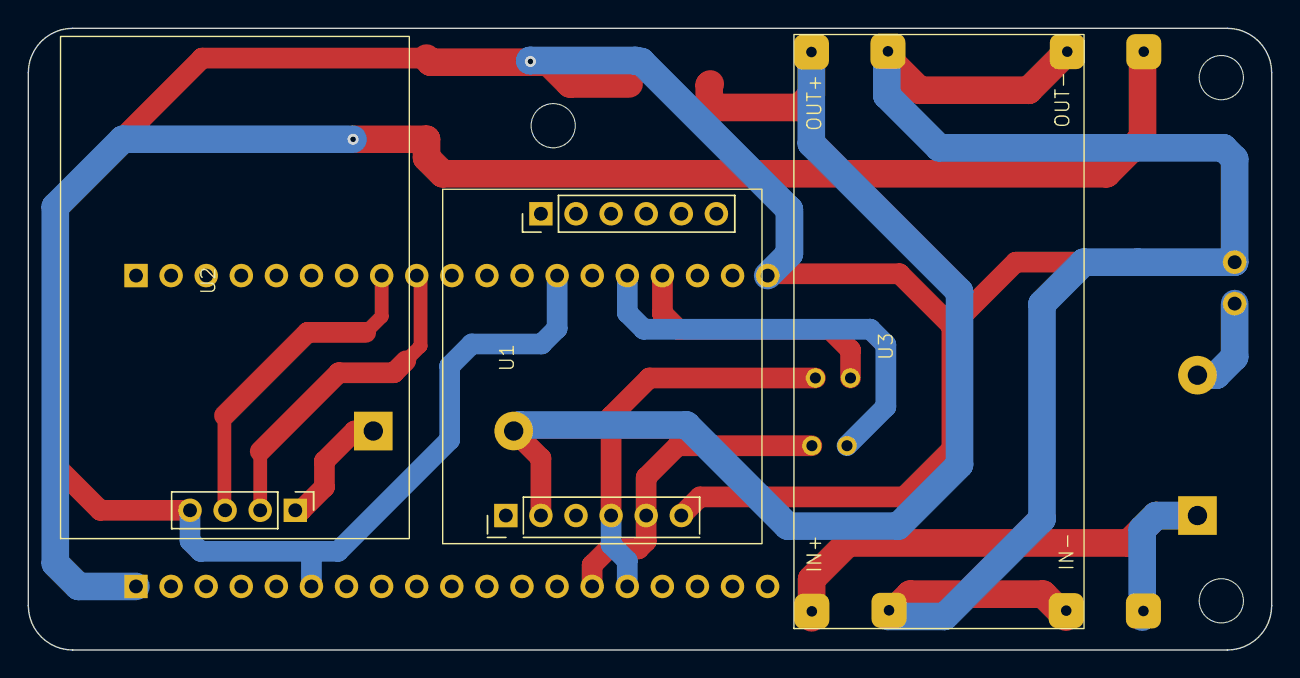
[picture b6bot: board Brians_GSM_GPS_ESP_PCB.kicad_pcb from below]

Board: 2 copper layers, 90.0 x 45.0 mm, 17 parts (3 on the bottom side), 12 nets.

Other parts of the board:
kibuzzard-65E188B0: G***; kibuzzard-65E188B0
kibuzzard-65E188EA: G***; kibuzzard-65E188EA

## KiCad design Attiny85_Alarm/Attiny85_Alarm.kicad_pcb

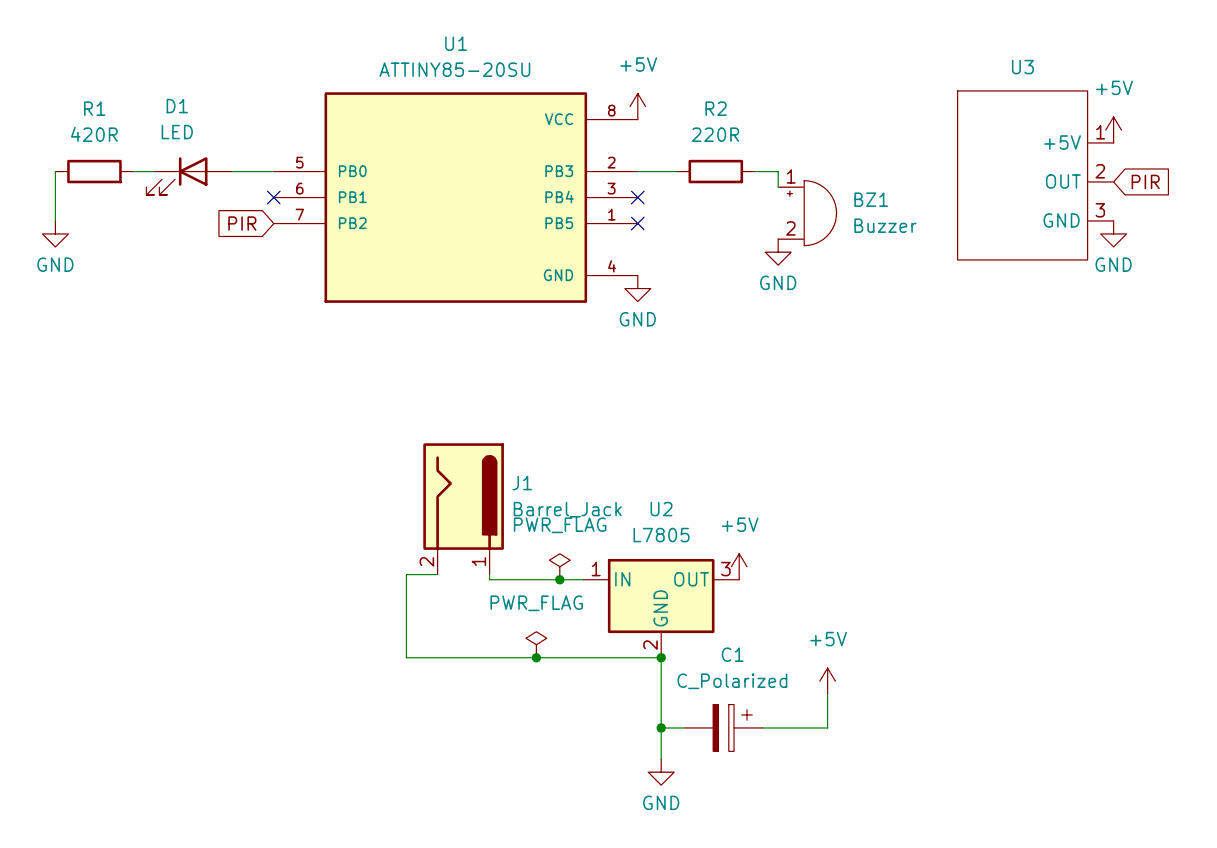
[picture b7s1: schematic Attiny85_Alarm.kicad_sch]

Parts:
BZ1: Buzzer; Buzzer_12x9.5RM7.6
C1: C_Polarized; CP_Radial_D5.0mm_P2.50mm
D1: LED; LED_D5.0mm
J1: Barrel_Jack; BarrelJack_SwitchcraftConxall_RAPC10U_Horizontal
R1: 420R; R_Axial_DIN0207_L6.3mm_D2.5mm_P2.54mm_Vertical
R2: 220R; R_Axial_DIN0204_L3.6mm_D1.6mm_P7.62mm_Horizontal
U1: ATTINY85-20SU; DIP-8_W7.62mm; PARTREV 2586Q–AVR–08/2013
U2: L7805; TO-220F-3_Horizontal_TabUp
U3: PIR_HC-SR501 MODULE

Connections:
+5V: C1.1, U1.8 (VCC), U2.3 (OUT), U3.1 (+5V)
GND: BZ1.2 (+), C1.2, J1.2, R1.1, U1.4 (GND), U2.2 (GND), U3.3 (GND)
unnamed: BZ1.1 (-), R2.2
unnamed: D1.2 (A), U1.5 (PB0)
unnamed: D1.1 (K), R1.2
unnamed: R2.1, U1.2 (PB3)
unnamed: J1.1, U2.1 (IN)
PIR: U1.7 (PB2), U3.2 (OUT)
